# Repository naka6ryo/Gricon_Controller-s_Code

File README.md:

# Gricon_Controller-s_Code

2024/12/27に桃山大学テック部主催で開催されたハッカソンに出展した作品 **Gricon** のコントローラー側プログラムです（2024/12/28 時点）。

このArduinoプログラムは、IMU（姿勢センサ）、曲げセンサ、モーターを統合し、姿勢推定・屈曲検出・振動出力を通じて新しい入力体験を提供します。

公式サイト：https://gricon.netlify.app/

## 🎥 デモ動画

---

## 🔗 関連リンク

- 🎮 **ゲーム側のプログラム（Unity）**  
  https://github.com/kdix-23-240/NewControllerProject-MomoyamaHack

- 📄 **作品に関する情報・ソースコードの解説・開発の流れの説明（Notion）**  
  https://flossy-band-678.notion.site/Gricon-Arduino-Unity-16a9ff2ca96c8032b9a5cc3768512383?pvs=4

---

## 📌 特徴 / Features

- **9軸IMUセンサ（LSM9DS1）** によるピッチ・ロール・ヨーの推定  
- **Madgwickフィルタ** による高精度な姿勢推定  
- **曲げセンサ** を使ったアナログ入力処理と平滑化  
- **加速度のグローバル変換・振動検出** によるリアクティブ入力対応  
- **振動モーター出力** を通じたハプティクスフィードバック  
- **シリアル通信** による外部機器（ゲーム）との双方向連携  

---

## 🔧 使用ハードウェア

- Arduino Nano 33 BLE Sense または LSM9DS1 搭載の互換ボード  
- 曲げセンサ（アナログ入力：A7）  
- 振動モーター（デジタル出力：D9）  
- 外部通信：Serial1（9600bps）

---

## 📷 回路図

以下は、本デバイスの回路図です（Arduino Nano 33 BLE + 曲げセンサ + モータ + Bluetooth構成）：

---

## 📤 センサ出力フォーマット

コントローラは以下のフォーマットで**バイナリ形式**のデータを送信します。

[S][pitch (2 bytes)][roll (2 bytes)][yaw (2 bytes)][bend (1 byte)]

- `S`: データ開始を示すヘッダ（1バイト）  
- `pitch`, `roll`, `yaw`: 姿勢角（各2バイト、0.1°単位）  
- `bend`: 曲げセンサ値（0〜20の範囲にクランプ）

---

## 🔁 モーター制御プロトコル（Serial1 受信）

シリアル経由で以下の1文字コマンドを送ることで、モーターの振動出力パターンを変更可能：

| コマンド | 周波数 (Hz相当) | デューティ比 | 内容             |
|----------|------------------|--------------|------------------|
| `'1'`    | 約25Hz           | 40%          | 弱い振動         |
| `'2'`    | 約50Hz           | 20%          | 中程度の振動     |
| `'3'`    | 約100Hz          | 12.5%        | 強い振動         |
| `'4'`    | 約125Hz          | 90%          | 連続振動         |
| その他    | -                | 0%           | モーター停止     |

---

## 🧭 キャリブレーション

プログラム開始時に自動実行され、地磁気・ジャイロのオフセットや曲げセンサの初期値を取得・補正します。

---

## 🔄 処理周期とスムージング

- 処理周期：1msごとのループ実行（約100Hz）  
- 各種センサ値に対してフィルタ係数を用いた平滑化処理あり  
- 姿勢角の推定には Madgwick フィルタを使用

---

## 🚀 セットアップコード例

```cpp
void setup() {
  Serial.begin(9600);       // デバッグ用
  Serial1.begin(9600);      // 外部機器との通信
  pinMode(motorPin, OUTPUT);
  initializeIMU();
  delay(100);
}
```

## 📚 使用ライブラリ

| ライブラリ名         | 説明                        | インストール方法                                     |
|----------------------|-----------------------------|------------------------------------------------------|
| Arduino_LSM9DS1      | IMU（加速度・ジャイロ・地磁気）センサ用 | Arduino IDE → ライブラリマネージャから検索して導入 |
| MadgwickAHRS         | 姿勢推定アルゴリズム        | Arduino IDE → ライブラリマネージャから検索して導入 |

---

## 📝 ライセンス

このプロジェクトは [MIT License](https://opensource.org/licenses/MIT) のもとで公開されています。

# Gricon Controller Code

This repository contains the **controller-side program** for **Gricon**, a project exhibited at a hackathon hosted by the **Momoyama University Tech Club** on **December 27, 2024** (status as of **December 28, 2024**).

This Arduino program integrates an **IMU (inertial measurement unit)**, a **flex sensor**, and a **vibration motor** to provide a new input experience through **orientation estimation**, **bend detection**, and **haptic feedback**.

Official site: https://gricon.netlify.app/

---

## 🎥 Demo Video

---

## 🔗 Related Links

- 🎮 **Game-side program (Unity)**  
  https://github.com/kdix-23-240/NewControllerProject-MomoyamaHack

- 📄 **Project details / source code explanation / development process (Notion)**  
  https://flossy-band-678.notion.site/Gricon-Arduino-Unity-16a9ff2ca96c8032b9a5cc3768512383?pvs=4

---

## 📌 Features

- **9-axis IMU (LSM9DS1)** for estimating **pitch / roll / yaw**
- **High-accuracy orientation estimation** using the **Madgwick filter**
- **Analog flex sensor processing** with smoothing
- **Global-frame acceleration conversion & vibration detection** for reactive input
- **Haptic feedback** via vibration motor output
- **Bidirectional communication** with external devices (e.g., a game) via **serial**

---

## 🔧 Hardware Used

- Arduino Nano 33 BLE Sense or a compatible board with LSM9DS1
- Flex sensor (analog input: A7)
- Vibration motor (digital output: D9)
- External communication: Serial1 (9600 bps)

---

## 📷 Circuit Diagram

Below is the circuit diagram for this device (Arduino Nano 33 BLE + flex sensor + motor + Bluetooth configuration):

---

## 📤 Sensor Output Format

The controller sends data in the following **binary** format:

`[S][pitch (2 bytes)][roll (2 bytes)][yaw (2 bytes)][bend (1 byte)]`

- `S`: 1-byte header indicating the start of a packet  
- `pitch`, `roll`, `yaw`: Euler angles (2 bytes each, in 0.1° units)  
- `bend`: flex sensor value (clamped to 0–20)

---

## 🔁 Motor Control Protocol (Serial1 Receive)

You can change the vibration output pattern by sending a **single-character command** over serial:

| Command | Frequency (approx.) | Duty Cycle | Description          |
|:------:|:---------------------|:----------:|----------------------|
| `'1'`  | ~25 Hz               | 40%        | Weak vibration       |
| `'2'`  | ~50 Hz               | 20%        | Medium vibration     |
| `'3'`  | ~100 Hz              | 12.5%      | Strong vibration     |
| `'4'`  | ~125 Hz              | 90%        | Continuous vibration |
| Other  | –                    | 0%         | Motor off            |

---

## 🧭 Calibration

Calibration runs automatically at startup to obtain and compensate:

- Magnetometer / gyroscope offsets  
- Initial baseline for the flex sensor  

---

## 🔄 Loop Rate & Smoothing

- Loop cycle: executed every 1 ms (≈ 100 Hz)  
- Sensor values are smoothed using filter coefficients  
- Orientation estimation uses the Madgwick filter

---

## 🚀 Setup Code Example

```cpp
void setup() {
  Serial.begin(9600);       // For debugging
  Serial1.begin(9600);      // Communication with external device
  pinMode(motorPin, OUTPUT);
  initializeIMU();
  delay(100);
}
```

📚 Libraries Used
Library	Description	Installation Method
Arduino_LSM9DS1	IMU (accel / gyro / magnetometer) library	Arduino IDE → Library Manager → search & install
MadgwickAHRS	AHRS orientation estimation algorithm	Arduino IDE → Library Manager → search & install
📝 License

This project is released under the MIT License:
https://opensource.org/licenses/MIT

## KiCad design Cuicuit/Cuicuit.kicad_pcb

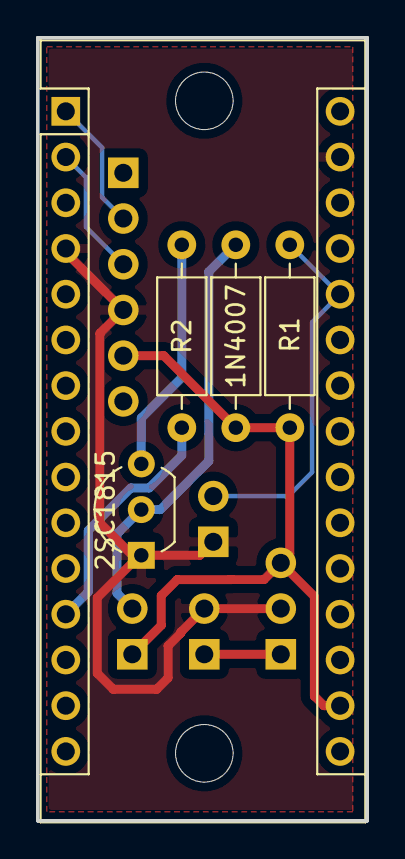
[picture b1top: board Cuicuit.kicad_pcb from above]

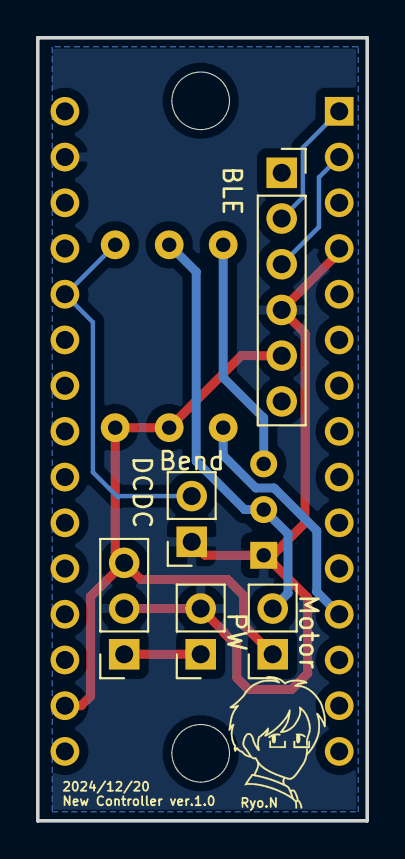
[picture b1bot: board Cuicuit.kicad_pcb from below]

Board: 2 copper layers, 18.3 x 43.5 mm, 12 parts (5 on the bottom side), 9 nets.

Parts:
1N4007: 1N4007; R_Axial_DIN0207_L6.3mm_D2.5mm_P10.16mm_Horizontal
2SC1815: 2SC1815; TO-92_Inline_Wide
Arduino_nano_33_ble1: Arduino_Nano_Every; Arduino_Nano
BLE: Conn_01x06_Female; PinSocket_1x06_P2.54mm_Vertical
Bend: Conn_01x02_Female; PinSocket_1x02_P2.54mm_Vertical
DCDC: Conn_01x03_Female; PinSocket_1x03_P2.54mm_Vertical
H1, H2: MountingHole; MountingHole_3.2mm_M3
Motor: Motor_DC; PinSocket_1x02_P2.54mm_Vertical
PW: Conn_01x02_Female; PinSocket_1x02_P2.54mm_Vertical
R1, R2: R; R_Axial_DIN0207_L6.3mm_D2.5mm_P10.16mm_Horizontal

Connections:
0: 2SC1815.1, Arduino_nano_33_ble1.4, Arduino_nano_33_ble1.29, BLE.4, Bend.1, DCDC.2, PW.2
+3.3VADC: 1N4007.2, Arduino_nano_33_ble1.17, BLE.5, DCDC.3, Motor.1, R1.2
+3V0: DCDC.1, PW.1
A7: Arduino_nano_33_ble1.26, Bend.2, R1.1
D9: Arduino_nano_33_ble1.12, R2.2
unnamed: 1N4007.1, 2SC1815.2, Motor.2
unnamed: 2SC1815.3, R2.1
RX: Arduino_nano_33_ble1.1, BLE.2
TX: Arduino_nano_33_ble1.2, BLE.3

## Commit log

2024-12-28 2024/12/28_First_message.md
2024-12-28 2024/12/28 ハッカソン時から改善したバージョン
2025-06-07 main
2025-06-07 AIによるコード改善（デバックなし）
2025-06-07 バイナリ通信への変更とコードの関数を用いた整理
2025-06-07 バイナリ通信の最適化（小数第1位まで）
2025-06-07 警告の振動数の調整
2025-06-07 握り具合の調整
2025-06-08 曲げセンサの閾値をゲーム側で制御
2025-06-08 曲げセンサの値の平滑化
2025-06-08 曲げセンサの範囲制限とそれによる通信の改良
2025-06-09 VScodeからの書き込み対応＆ヨー方向の制御系統の変更
2025-06-09 VScodeでの書き込み対応
2025-06-14 VScode上での書き込み用アップデート
2025-06-14 地磁気補正の改良
2025-06-14 地磁気キャリブレーションの更新及び初期値の配列化
2025-06-15 ピッチに応じたゲイン調整の導入
2025-06-15 曲げセンサの小数化
2025-06-15 ゲインのピッチ変化の削除
2025-06-15 待機時間の延長
2025-06-30 ヨー角の他角度の連動の修正
2025-10-09 近大プロトコン用更新
2026-01-13 Add Hard and Circuit
2026-01-30 Update README with project details and links
2026-01-30 Add library usage and license sections to README
    Added library usage section and license information.
